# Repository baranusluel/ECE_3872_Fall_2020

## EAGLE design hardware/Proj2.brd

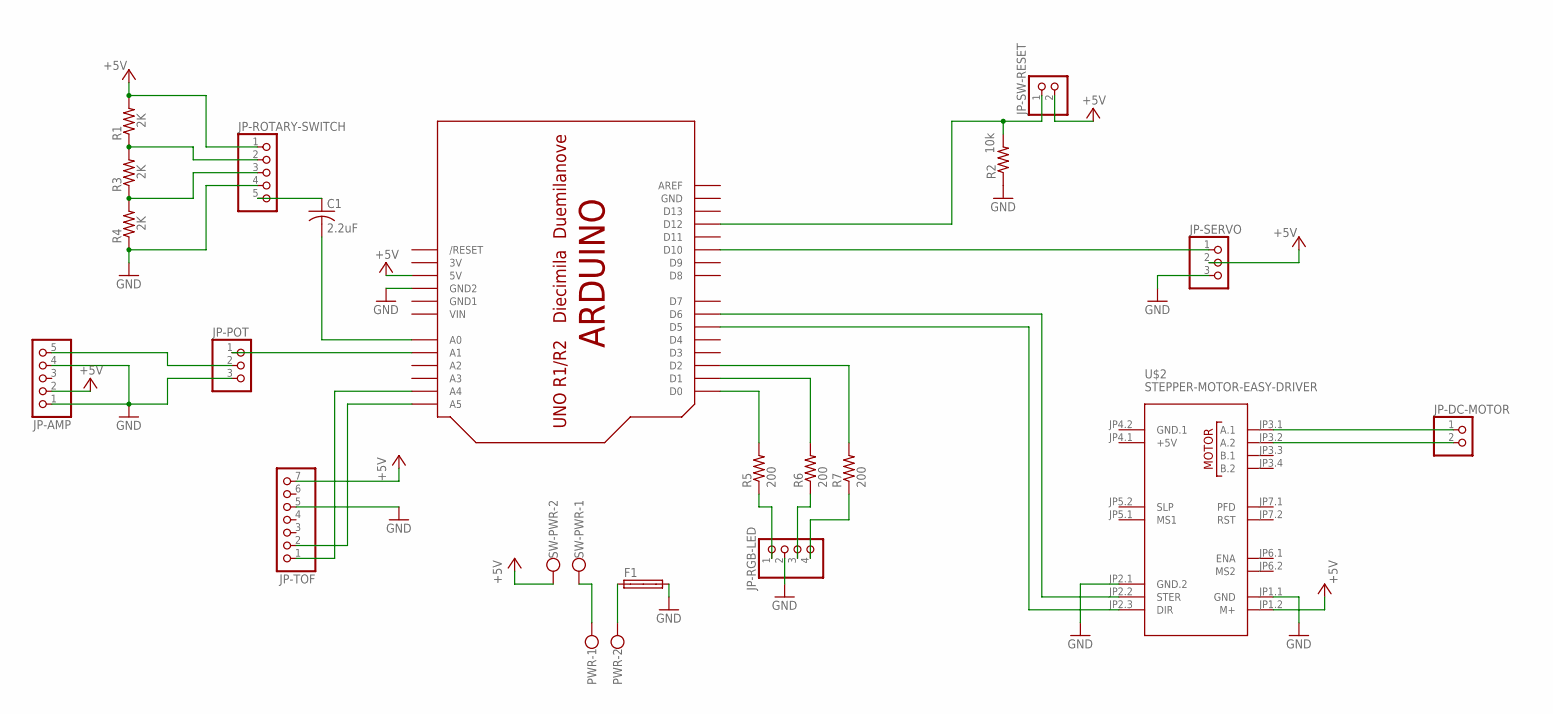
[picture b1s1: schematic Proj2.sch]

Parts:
C1: 2.2uF; C050-024X044
F1: SH32
JP-AMP: PINHD-1X5; 1X05
JP-DC-MOTOR: PINHD-1X2; 1X02
JP-POT: PINHD-1X3; 1X03
JP-RGB-LED: PINHD-1X4; 1X04
JP-ROTARY-SWITCH: PINHD-1X5; 1X05
JP-SERVO: PINHD-1X3; 1X03
JP-SW-RESET: PINHD-1X2; 1X02
JP-TOF: PINHD-1X7; 1X07
PWR: W237-102
R1, R3, R4: 2K; 0207/7
R2: 10k; 0207/7
R5, R6, R7: 200; 0207/7
SW-PWR: W237-102
U$1: ARDUINO-NOHOLE
U$2: STEPPER-MOTOR-EASY-DRIVER

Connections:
3V: U$1.3V
+5V: JP-AMP.2, JP-ROTARY-SWITCH.1, JP-SERVO.2, JP-SW-RESET.2, JP-TOF.7, R1.2, SW-PWR.2, U$1.5V, U$2.JP1.2 (M+)
GND: F1.2A, JP-AMP.1, JP-AMP.4, JP-POT.3, JP-RGB-LED.2, JP-ROTARY-SWITCH.4, JP-SERVO.3, JP-TOF.5, R2.1, R4.1, U$1.GND, U$1.GND2, U$2.JP1.1 (GND), U$2.JP2.1 (GND.2)
GND1: U$1.GND1
unnamed: JP-TOF.1, U$1.A4
unnamed: JP-TOF.2, U$1.A5
unnamed: PWR.1, SW-PWR.1
unnamed: JP-RGB-LED.1, R5.1
unnamed: F1.1A, PWR.2
unnamed: C1.1, JP-ROTARY-SWITCH.5
unnamed: R5.2, U$1.D0
unnamed: JP-SERVO.1, U$1.D10
unnamed: JP-RGB-LED.3, R6.1
unnamed: R6.2, U$1.D1
unnamed: R7.2, U$1.D2
unnamed: U$1.D5, U$2.JP2.3 (DIR)
unnamed: JP-POT.1, U$1.A1
unnamed: JP-SW-RESET.1, R2.2, U$1.D12
unnamed: JP-RGB-LED.4, R7.1
unnamed: C1.2, U$1.A0
unnamed: JP-AMP.5, JP-POT.2
unnamed: JP-ROTARY-SWITCH.2, R1.1, R3.2
unnamed: JP-ROTARY-SWITCH.3, R3.1, R4.2
unnamed: U$1.D6, U$2.JP2.2 (STER)
unnamed: JP-DC-MOTOR.2, U$2.JP3.2 (A.2)
unnamed: JP-DC-MOTOR.1, U$2.JP3.1 (A.1)
VIN: U$1.VIN

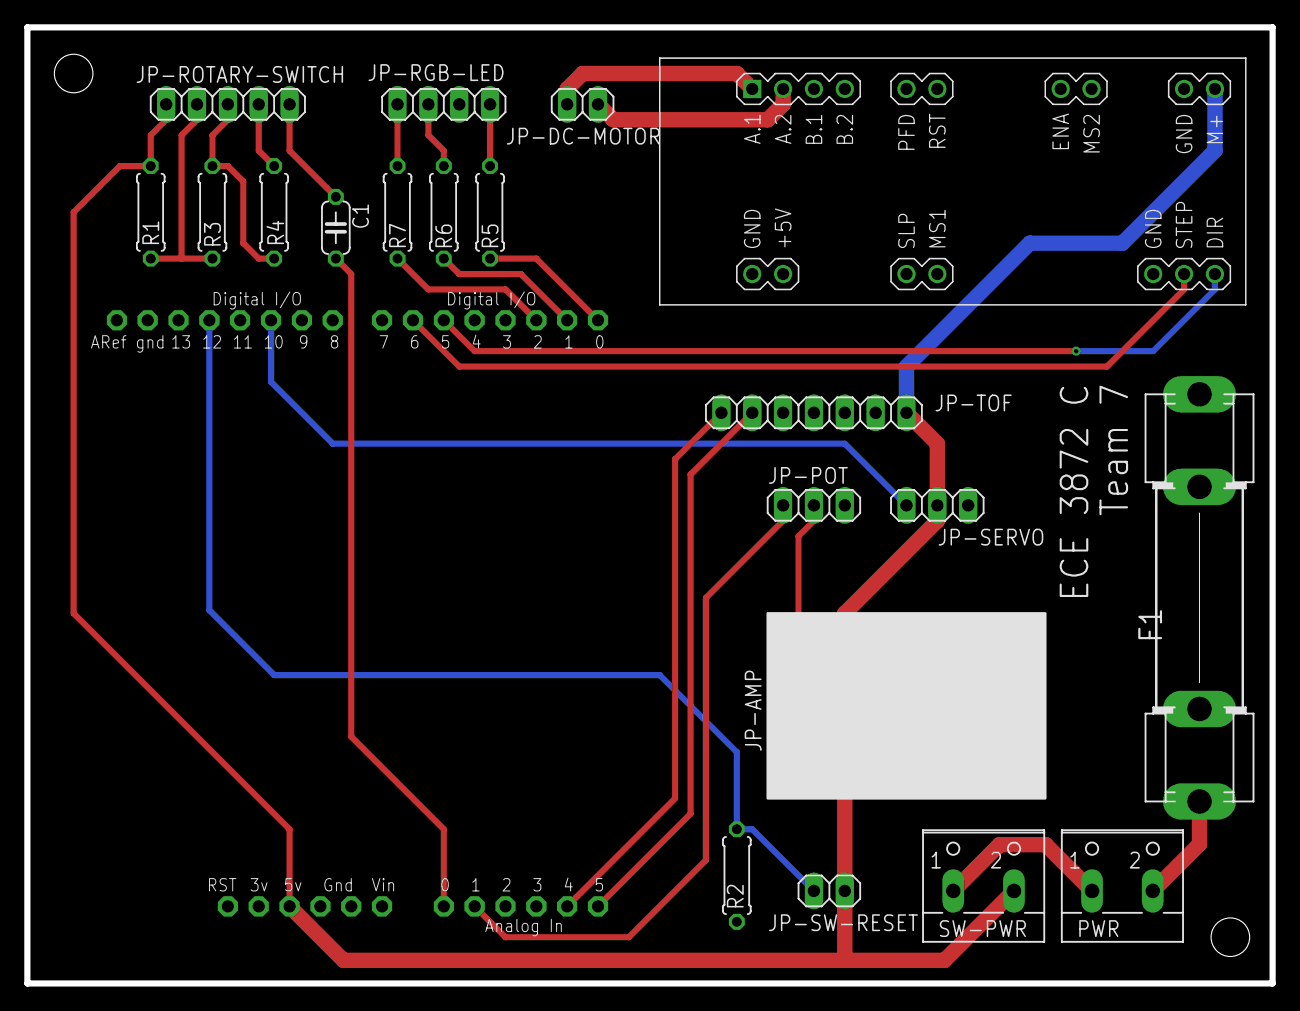
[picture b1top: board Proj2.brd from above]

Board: 2 copper layers, 102.5 x 78.7 mm, 21 parts (0 on the bottom side), 24 nets.

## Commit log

2020-09-21 Add Proteus schematic
2020-09-21 Add initial controller software with state management
2020-09-23 Add audio record / playback capability
2020-09-23 Fix audio playback issue due to state transition bug
2020-09-23 Add motor control tied to audio
2020-09-24 Add audio output in play live state
2020-09-24 Modify reset button behavior for entering idle state
2020-10-01 added schematic for pcb
2020-10-08 Revise schematic to use pin headers and other connectors, correct motor driver, and resistor ladder for rotary switch
2020-10-08 Design PCB rev1
2020-10-08 Revisions from meeting, generate CAM files
2020-10-10 Revise trace widths, power plane, fuse footprint after meeting with James
2020-10-22 Add final CAM files
2020-11-02 Integrating SW with HW, 11/1 meeting
2020-11-03 Bug fixes from tuesday meeting
2020-11-05 Final version for demo

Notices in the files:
parts and their libraries:
diy-modules: Released under the Creative Commons Attribution 4.0 International License: http://creativecommons.org/licenses/by/4.0
